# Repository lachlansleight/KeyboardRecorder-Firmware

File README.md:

# MIDI Recorder Firmware + CAD

My MIDI recorder is a small device that lives plugged into a MIDI instrument (specifically a digital piano) and automatically records and uploads everything played on it for later reference. The core idea is that no input is required, and no feedback is given that recording has started/stopped, so you get 'recording-by-default'. A webserver automatically processes recordings and makes them available for playback via a frontend website.

---

This is the firmware and CAD files for a device that I'm building that automatically records everything I play on my piano. The repository for the server and frontend website can be found [here](https://github.com/lachlansleight/MidiRecorder-Server)

The device is pretty simple - it's an ESP32, some power regulation and MIDI IN / MIDI THRU. Check back soon, I'm actively working on this project right now so CAD files for the enclosure should be coming soon!

### Bill of Materials

  * ESP32 WROOM (or similar) - note the pinout if you're using my PCB design
  * 6N138 Optocoupler (DIP8)
  * HT7333 Linear Voltage Regulator
  * 1N914 Signal Diode
  * 6 x 220Ω Resistors
  * 4-pin 8mm RGB LED
  * Bidirectional Logic Level Converter (e.g. [this one from sparkfun](https://www.sparkfun.com/products/12009))
  * 2 x 5-pin DIN Jack (panel mount)
  * 1 x DC Barrel Jack (panel mount)
  * 5V 2A DC Power Supply (make sure the barrel size matches your jack size)

### Firmware Setup

  1. Open up the firmware in the Arduino IDE and install [this custom library](https://github.com/FortySevenEffects/arduino_midi_library) (you should be able to find it in the Library Manager
  2. Replace my SSID and passcode with your WiFi credentials (2.4GHz only)
  3. Replace the server with the URL of your custom server instance (see the [server readme for details](https://github.com/lachlansleight/MidiRecorder-Server))
  4. Make sure that line 1 is uncommented (i.e. that `DEBUG_MODE` is defined)
  5. Flash the firmware and examine the serial output (38400 baud) - note the MAC address and ensure WiFi is connecting successfully (reboot the device if you don't see them)
  7. Update the `NEXT_PUBLIC_DEVICE_MAC_ADDRESS` environment variable on the server and redeploy
  8. Try uploading a recording! If it works, comment-out `DEBUG_MODE` and reflash - you're done!

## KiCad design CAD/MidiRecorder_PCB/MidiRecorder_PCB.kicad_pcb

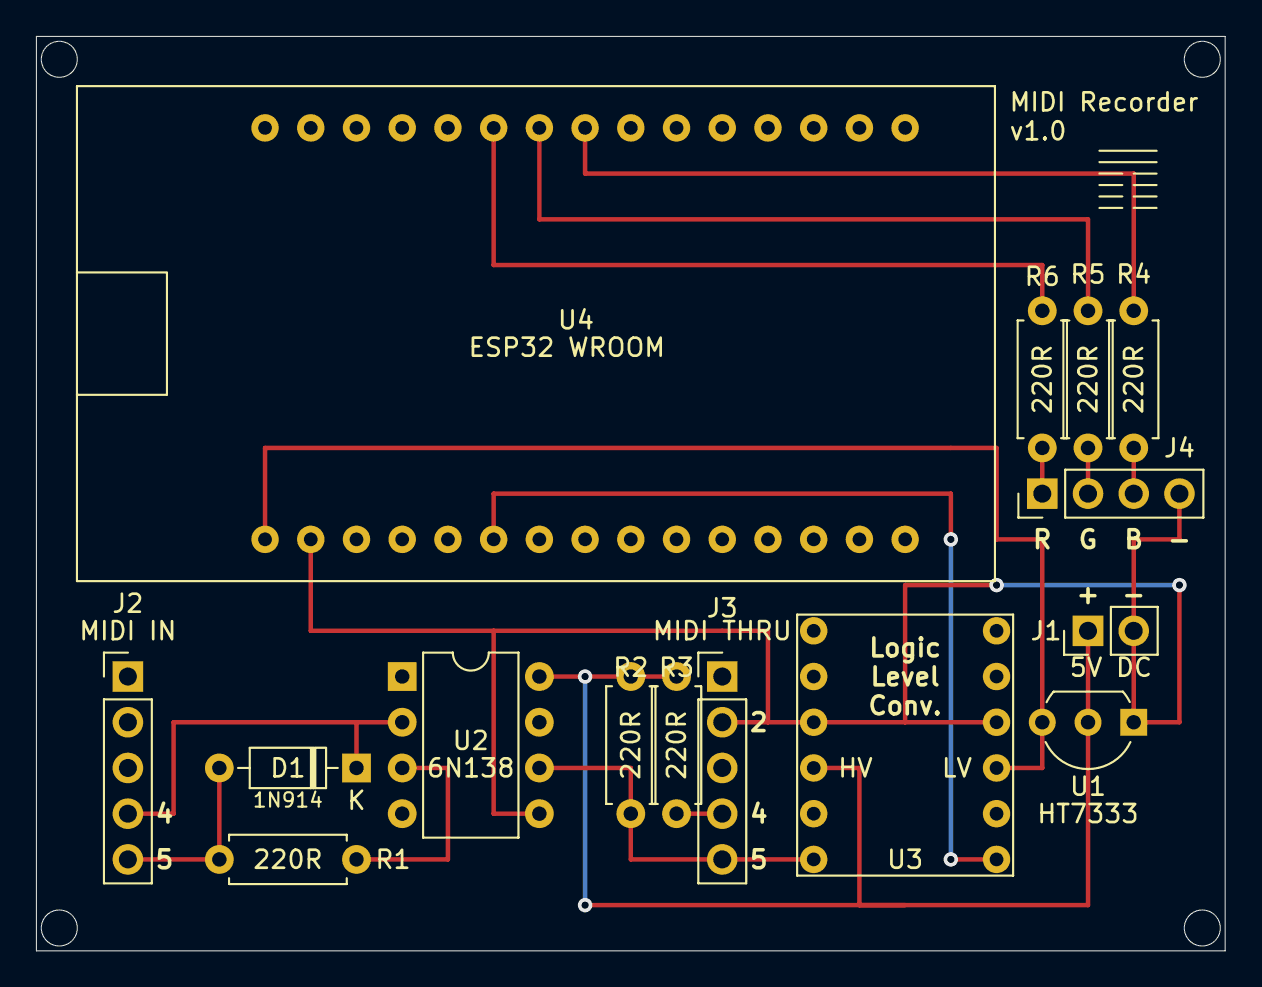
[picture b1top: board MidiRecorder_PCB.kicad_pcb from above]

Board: 2 copper layers, 66.0 x 50.8 mm, 15 parts (0 on the bottom side), 15 nets.

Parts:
D1: 1N914; D_DO-35_SOD27_P7.62mm_Horizontal
J1: 5V DC; PinHeader_1x02_P2.54mm_Vertical
J2: MIDI IN; PinHeader_1x05_P2.54mm_Vertical
J3: MIDI THRU; PinHeader_1x05_P2.54mm_Vertical
J4: RGB OUT; PinHeader_1x04_P2.54mm_Vertical
R1, R2, R3, R4, R5, R6: 220R; R_Axial_DIN0207_L6.3mm_D2.5mm_P7.62mm_Horizontal
U1: HT7333; TO-92L_Inline_Wide
U2: 6N138; DIP-8_W7.62mm
U3: LogicLevelConverter; LogicLevelShifter
U4: ESP32 WROOM; ESP32WROOM

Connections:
+3V3: U1.3, U3.3, U4.1
+5V: J1.1, R2.1, R3.2, U1.2, U2.8, U3.10
GND: J1.2, J3.2, J4.4, U1.1, U2.5, U3.4, U3.9, U4.2
MIDISERIAL: J3.5, R2.2, U2.6, U3.12
unnamed: D1.1, J2.4, U2.2
unnamed: D1.2, J2.5, R1.2
unnamed: J3.4, R3.1
unnamed: J4.1, R6.1
unnamed: J4.2, R5.1
unnamed: J4.3, R4.1
unnamed: R1.1, U2.3
unnamed: R4.2, U4.23
unnamed: R5.2, U4.24
unnamed: R6.2, U4.25
unnamed: U3.1, U4.6

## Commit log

2021-03-23 feat: Basic ESP32 MIDI Input working
    + Holy fucking god that was annoying
2021-03-23 feat: Get song recording + POSTing working
2021-03-23 fix: Make recordings not upload if they have less than 10 messages
2021-03-24 feat: Use the actual webserver
2021-03-24 feat: Add RGB LED and maybe improve message count problem with calloc
2021-03-24 feat: Wrap all the debug stuff in a #define
2021-03-25 feat: Add initial version of PCB (untested)
2021-03-25 fix: Improve render outline
2021-03-25 fix: Minor PCB updates
2021-03-25 fix: Update LED pins to match PCB
2021-03-25 fix: Disconnect 5V from 3V3 oops
2021-04-09 feat: Add MAC address as authorization header
2021-04-09 feat: Calculate song time at moment of MIDI message reception
2021-04-09 feat: Add 400 and 500 error reporting
